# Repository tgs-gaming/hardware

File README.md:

# TGS Hardware

TGS Hardware Projects

[Documentation](docs/README.md)

## TGS INPUT board

[INPUT BOARD USAGE MANUAL](docs/tgs_input_board_usage_manual.md)

Board Configuration Tool

## 

## TGS INPUT/OUTPUT board

## TGS OUTPUT board

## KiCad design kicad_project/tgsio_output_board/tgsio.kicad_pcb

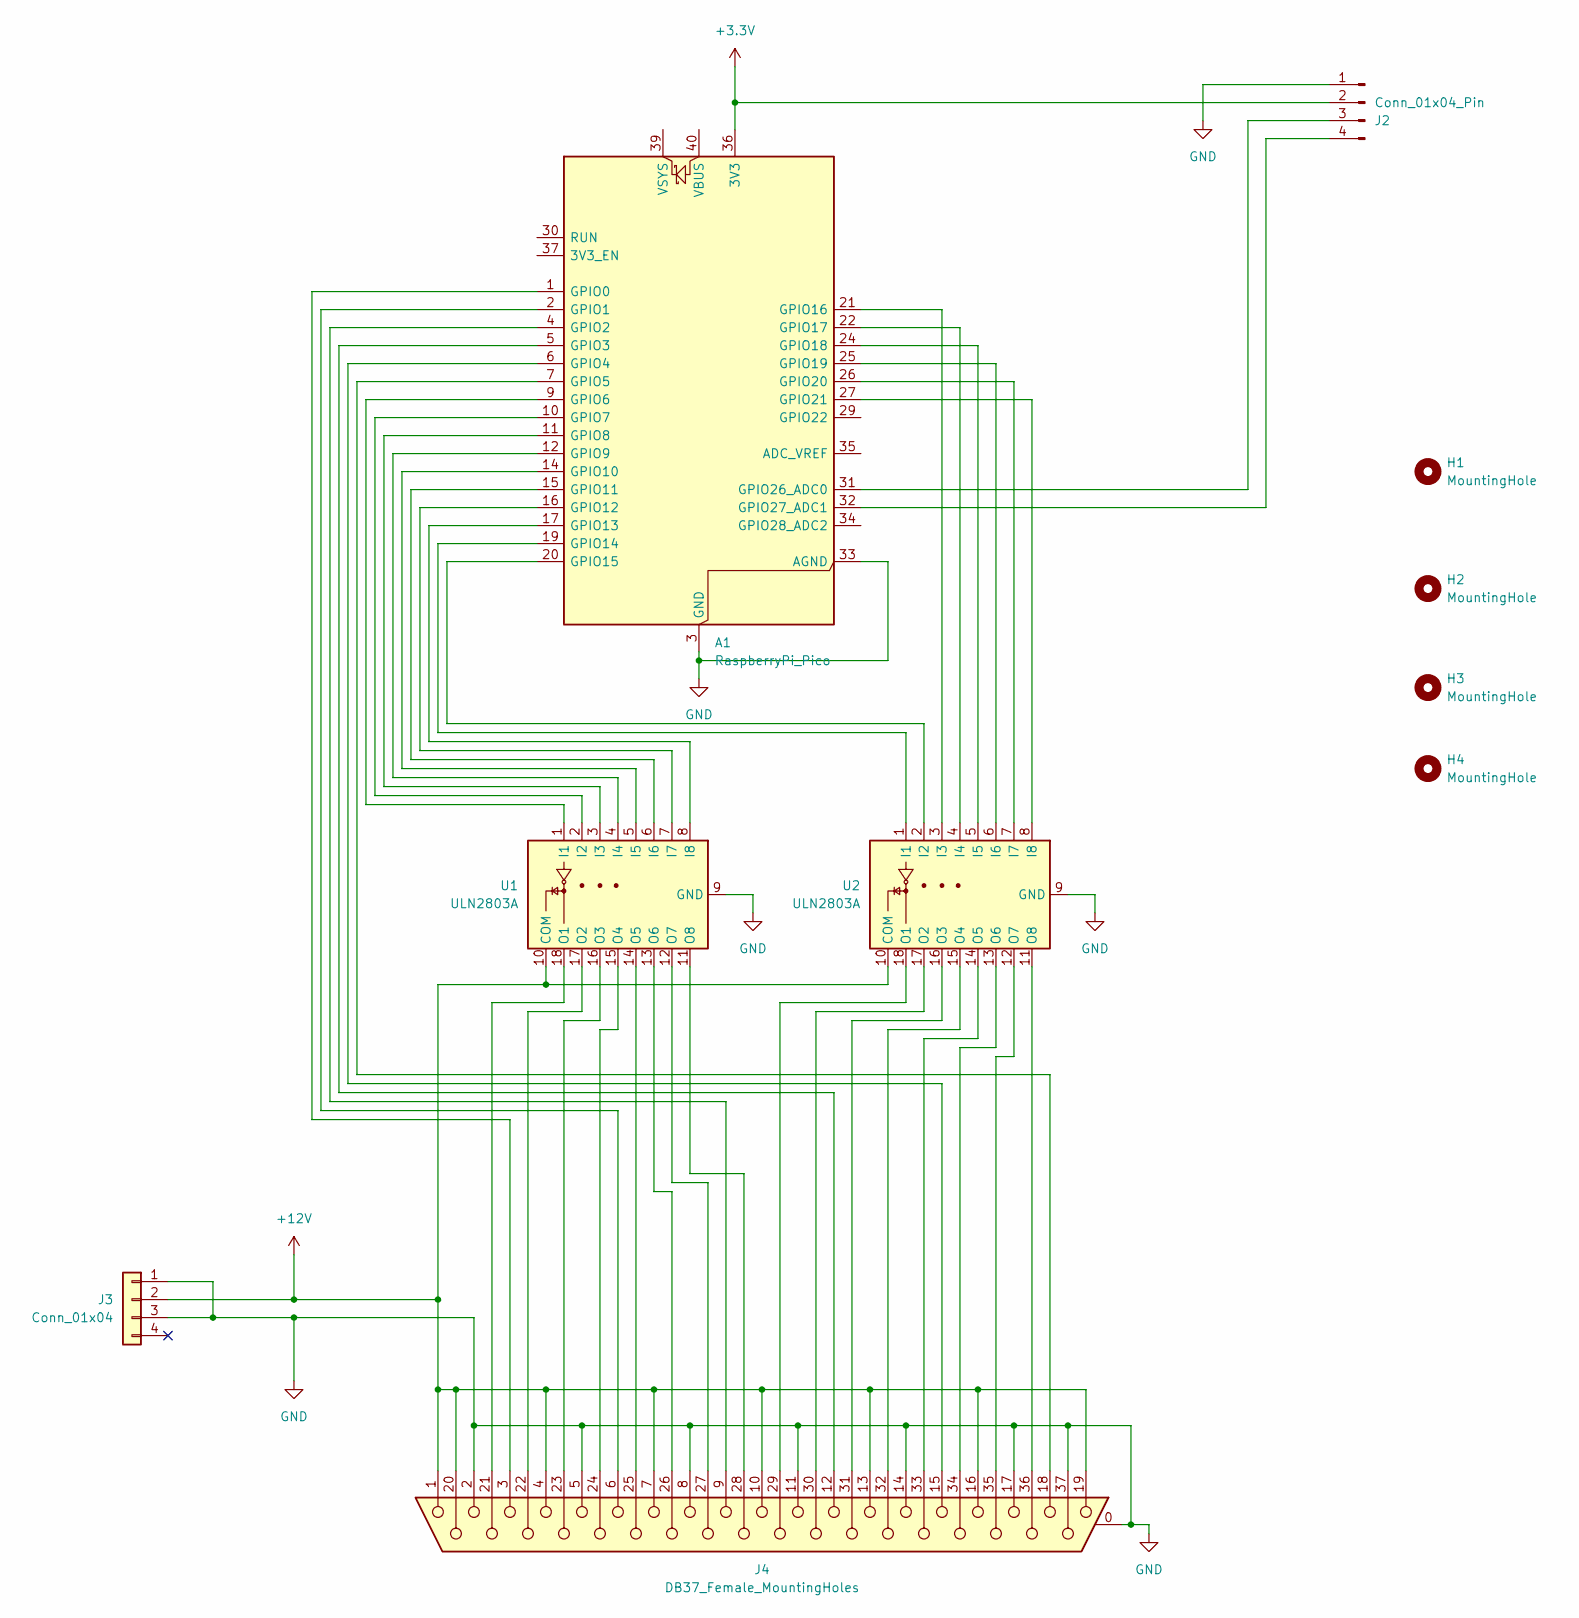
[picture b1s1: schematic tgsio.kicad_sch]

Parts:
A1: RaspberryPi_Pico; RaspberryPi_Pico_Common_Unspecified
H1, H2, H3, H4: MountingHole; MountingHole_3.2mm_M3
J2: Conn_01x04_Pin; JST_PH_B4B-PH-K_1x04_P2.00mm_Vertical
J3: Conn_01x04; Molex_Mini-Fit_Jr_5566-04A_2x02_P4.20mm_Vertical
J4: DB37_Female_MountingHoles; DSUB-37_Female_Horizontal_P2.77x2.84mm_EdgePinOffset4.94mm_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
U1, U2: ULN2803A; DIP-18_W7.62mm_LongPads

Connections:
+3.3V: A1.36 (3V3), J2.2
+12V: J3.2, J4.1, J4.4, J4.7, J4.10, J4.13, J4.16, J4.19, J4.20, U1.10 (COM), U2.10 (COM)
GND: A1.3 (GND), A1.8 (GND), A1.13 (GND), A1.18 (GND), A1.23 (GND), A1.28 (GND), A1.33 (AGND), A1.38 (GND), J2.1, J3.1, J3.3, J4.0 (PAD), J4.2, J4.5, J4.8, J4.11, J4.14, J4.17, J4.37, U1.9 (GND), U2.9 (GND)
unnamed: A1.1 (GPIO0), J4.3
unnamed: A1.2 (GPIO1), J4.6
unnamed: A1.4 (GPIO2), J4.9
unnamed: A1.5 (GPIO3), J4.12
unnamed: A1.6 (GPIO4), J4.15
unnamed: A1.7 (GPIO5), J4.18
unnamed: A1.9 (GPIO6), U1.1 (I1)
unnamed: A1.10 (GPIO7), U1.2 (I2)
unnamed: A1.11 (GPIO8), U1.3 (I3)
unnamed: A1.12 (GPIO9), U1.4 (I4)
unnamed: A1.14 (GPIO10), U1.5 (I5)
unnamed: A1.15 (GPIO11), U1.6 (I6)
unnamed: A1.16 (GPIO12), U1.7 (I7)
unnamed: A1.17 (GPIO13), U1.8 (I8)
unnamed: A1.19 (GPIO14), U2.1 (I1)
unnamed: A1.20 (GPIO15), U2.2 (I2)
unnamed: A1.21 (GPIO16), U2.3 (I3)
unnamed: A1.22 (GPIO17), U2.4 (I4)
unnamed: A1.24 (GPIO18), U2.5 (I5)
unnamed: A1.25 (GPIO19), U2.6 (I6)
unnamed: A1.26 (GPIO20), U2.7 (I7)
unnamed: A1.27 (GPIO21), U2.8 (I8)
unnamed: A1.31 (GPIO26_ADC0), J2.3
unnamed: A1.32 (GPIO27_ADC1), J2.4
unnamed: J4.21, U1.18 (O1)
unnamed: J4.22, U1.17 (O2)
unnamed: J4.23, U1.16 (O3)
unnamed: J4.24, U1.15 (O4)
unnamed: J4.25, U1.14 (O5)
unnamed: J4.26, U1.13 (O6)
unnamed: J4.27, U1.12 (O7)
unnamed: J4.28, U1.11 (O8)
unnamed: J4.29, U2.18 (O1)
unnamed: J4.30, U2.17 (O2)
unnamed: J4.31, U2.16 (O3)
unnamed: J4.32, U2.15 (O4)
unnamed: J4.33, U2.14 (O5)
unnamed: J4.34, U2.13 (O6)
unnamed: J4.35, U2.12 (O7)
unnamed: J4.36, U2.11 (O8)

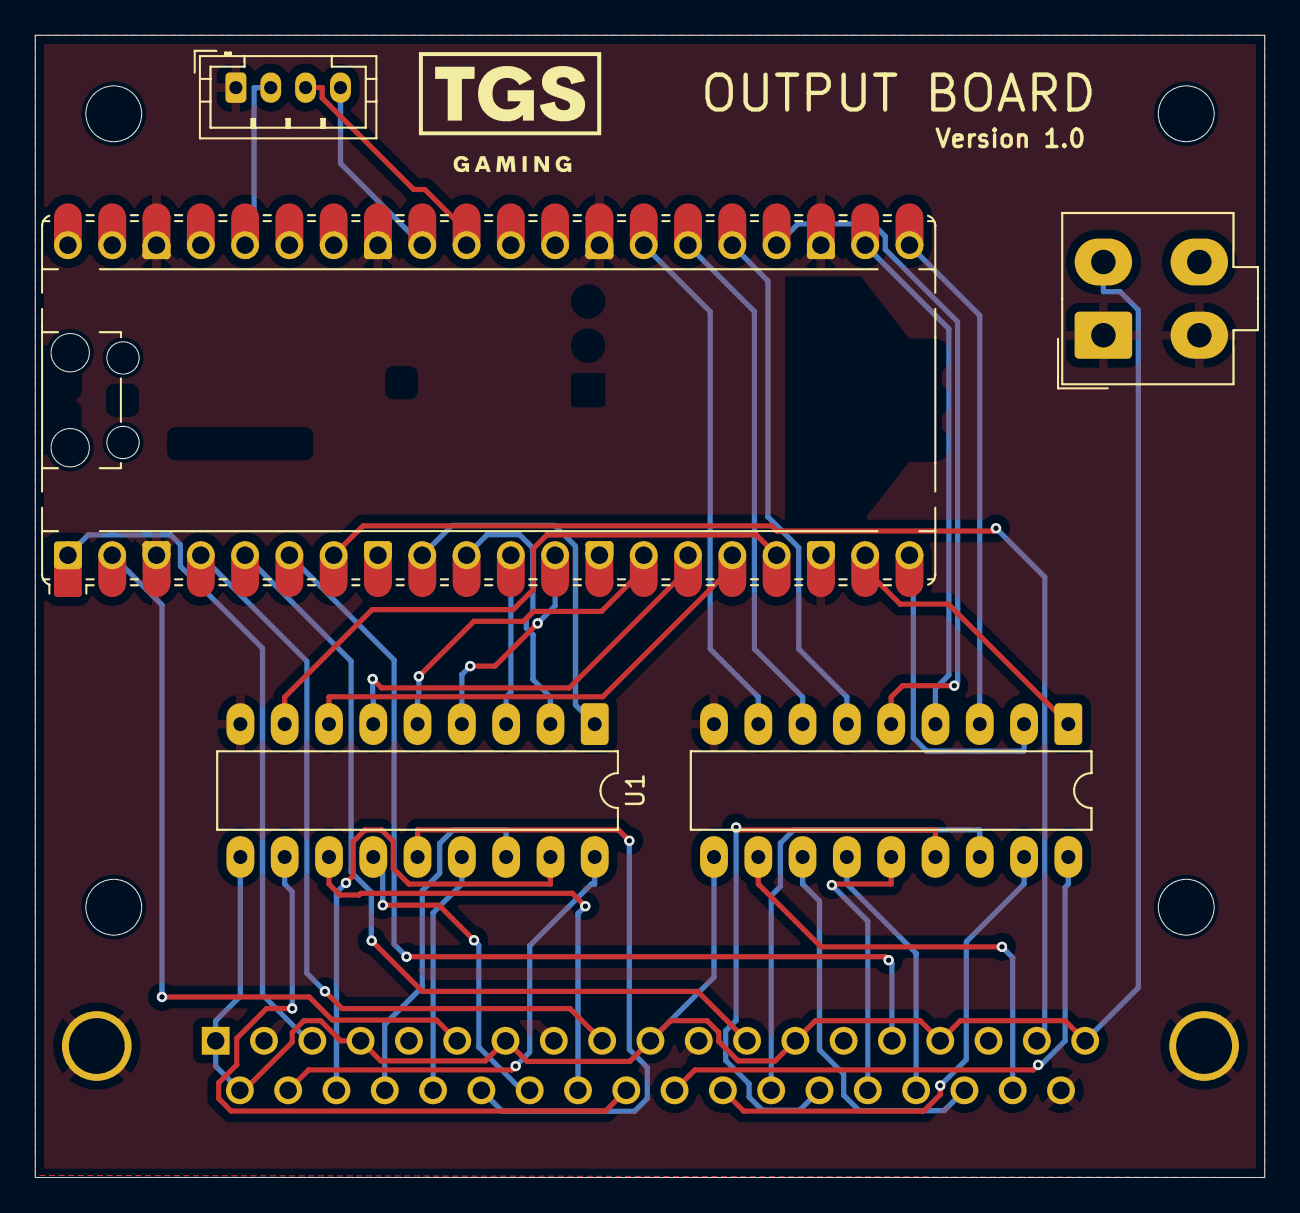
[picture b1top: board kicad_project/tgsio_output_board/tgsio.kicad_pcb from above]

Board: 2 copper layers, 70.5 x 65.5 mm, 10 parts (1 on the bottom side), 43 nets.

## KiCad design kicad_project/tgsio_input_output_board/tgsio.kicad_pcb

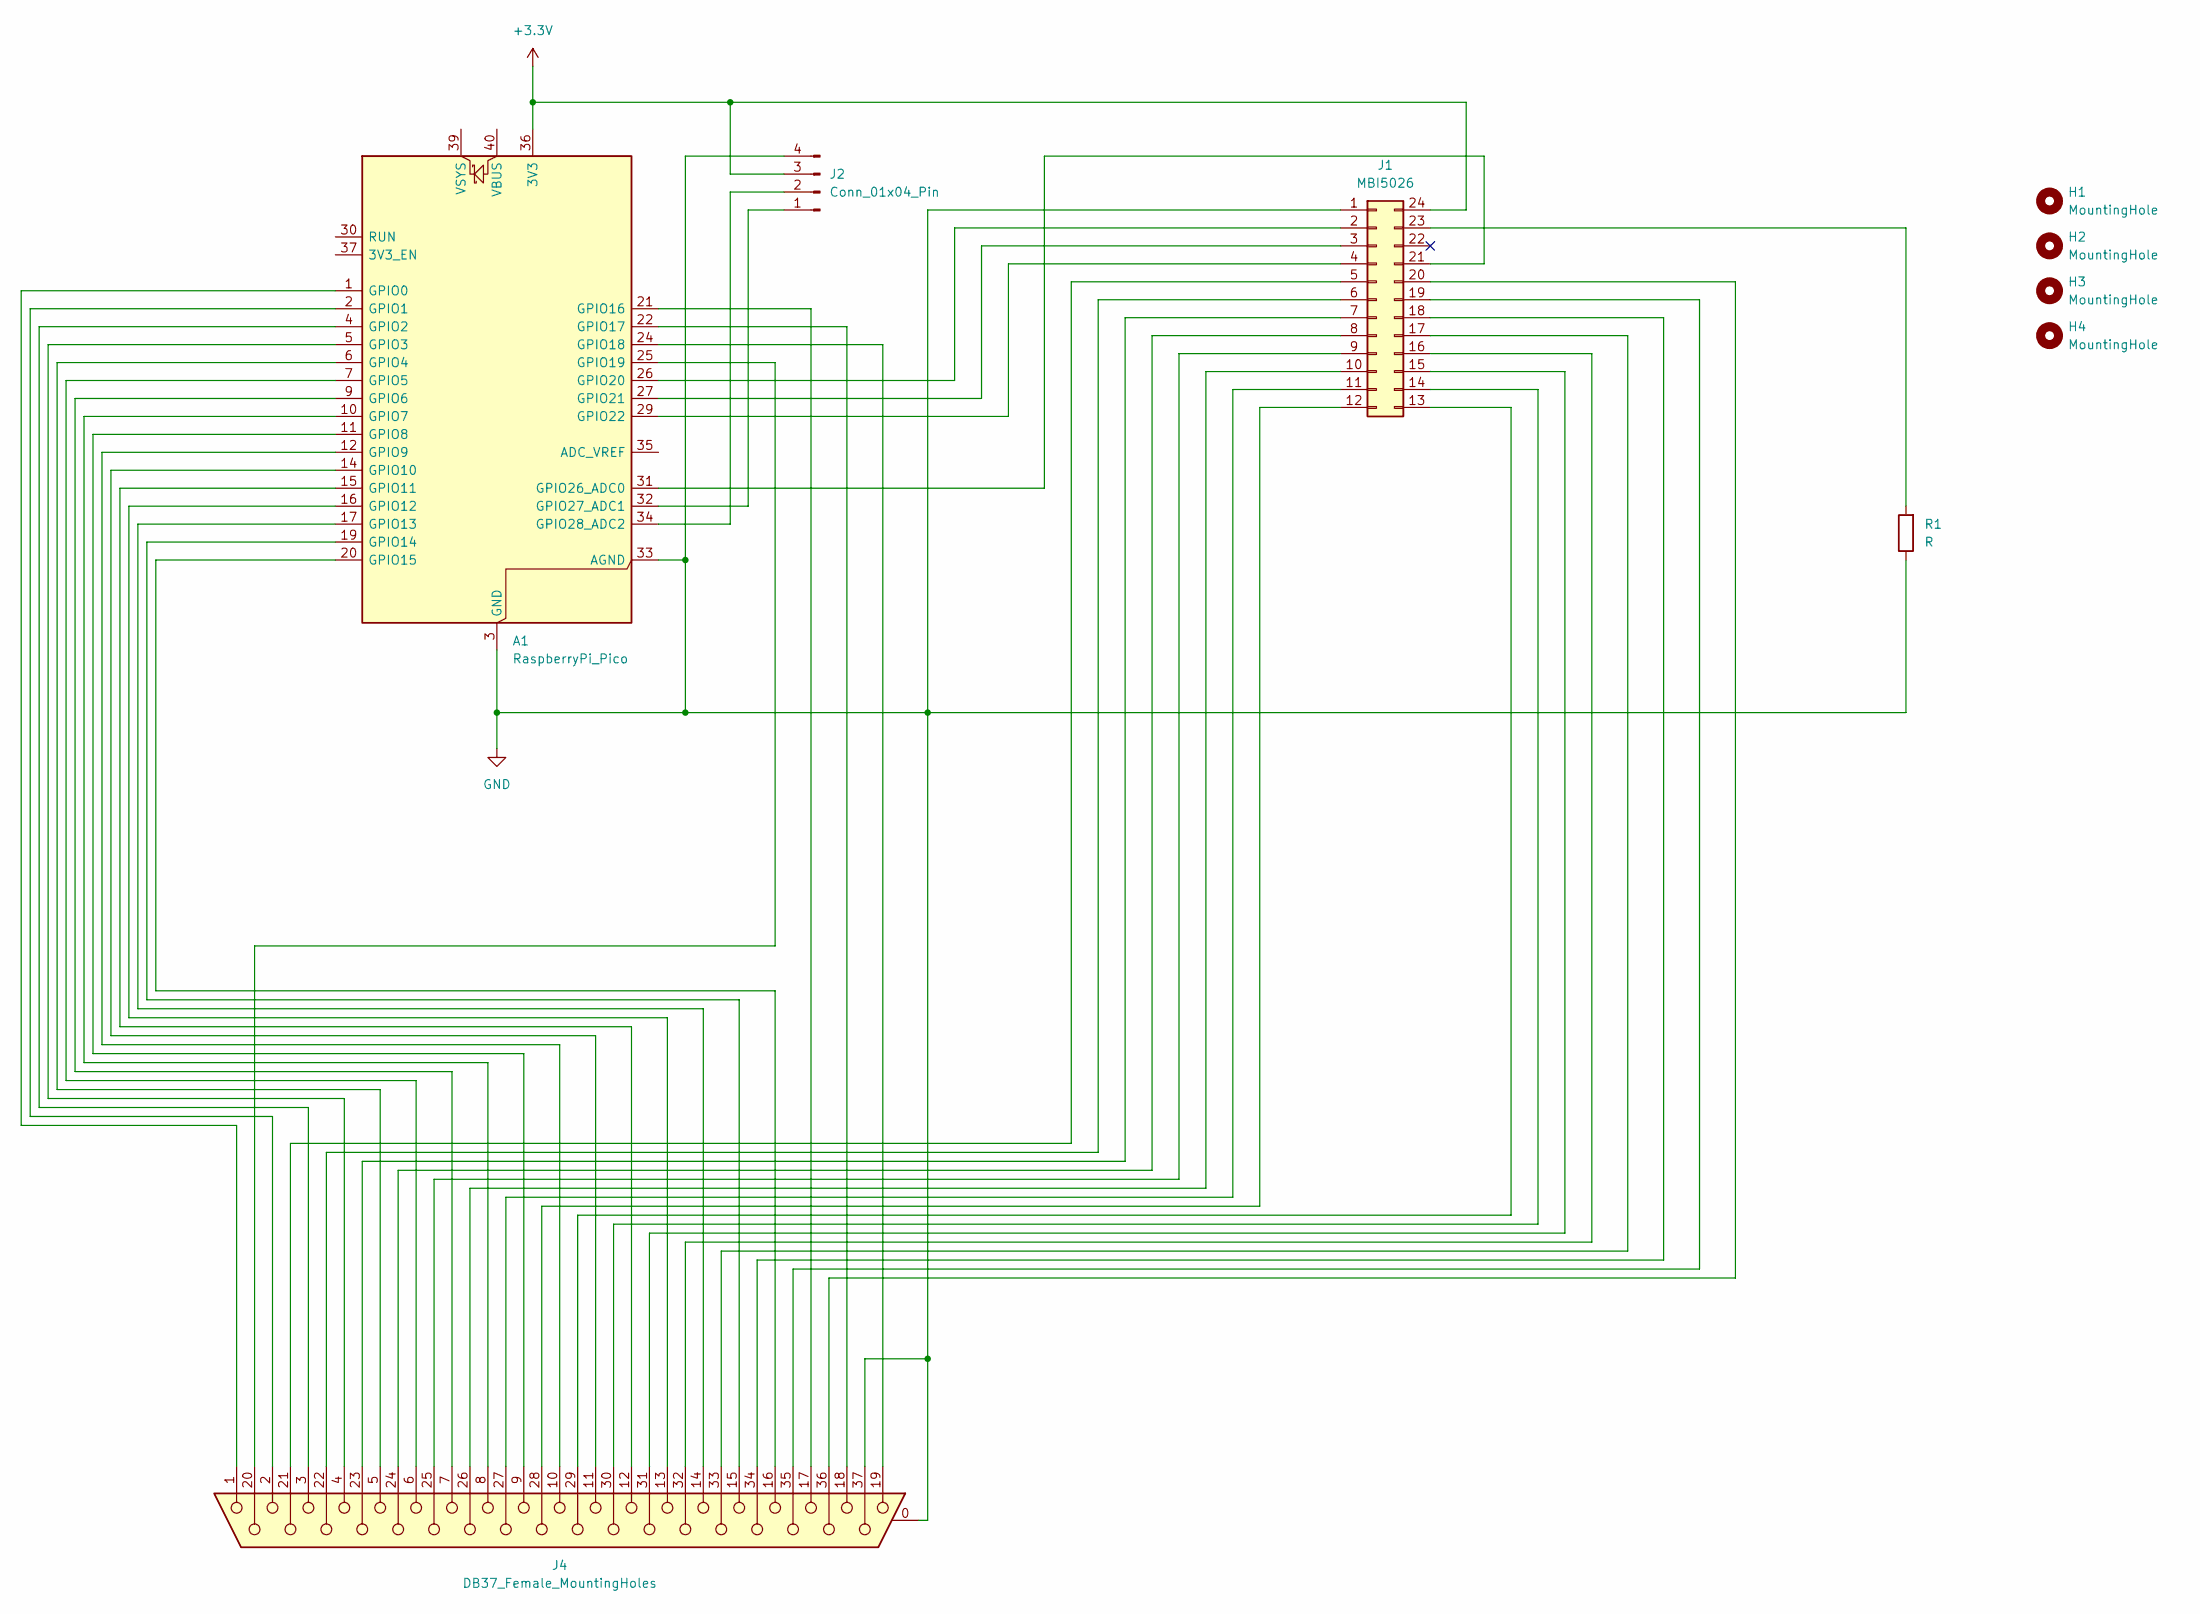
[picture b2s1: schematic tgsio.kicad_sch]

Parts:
A1: RaspberryPi_Pico; RaspberryPi_Pico_Common_SMD
H1, H2, H3, H4: MountingHole; MountingHole_3.2mm_M3
J1: MBI5026; DIP-24_W7.62mm_LongPads
J2: Conn_01x04_Pin; JST_PH_B4B-PH-K_1x04_P2.00mm_Vertical
J4: DB37_Female_MountingHoles; DSUB-37_Female_Horizontal_P2.77x2.84mm_EdgePinOffset4.94mm_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
R1: R; R_Axial_DIN0207_L6.3mm_D2.5mm_P10.16mm_Horizontal

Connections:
+3.3V: A1.36 (3V3), J1.24, J2.3
GND: A1.3 (GND), A1.8 (GND), A1.13 (GND), A1.18 (GND), A1.23 (GND), A1.28 (GND), A1.33 (AGND), A1.38 (GND), J1.1, J2.4, J4.0 (PAD), J4.37, R1.1
unnamed: A1.1 (GPIO0), J4.1
unnamed: A1.2 (GPIO1), J4.2
unnamed: A1.4 (GPIO2), J4.3
unnamed: A1.5 (GPIO3), J4.4
unnamed: A1.6 (GPIO4), J4.5
unnamed: A1.7 (GPIO5), J4.6
unnamed: A1.9 (GPIO6), J4.7
unnamed: A1.10 (GPIO7), J4.8
unnamed: A1.11 (GPIO8), J4.9
unnamed: A1.12 (GPIO9), J4.10
unnamed: A1.14 (GPIO10), J4.11
unnamed: A1.15 (GPIO11), J4.12
unnamed: A1.16 (GPIO12), J4.13
unnamed: A1.17 (GPIO13), J4.14
unnamed: A1.19 (GPIO14), J4.15
unnamed: A1.20 (GPIO15), J4.16
unnamed: A1.21 (GPIO16), J4.17
unnamed: A1.22 (GPIO17), J4.18
unnamed: A1.24 (GPIO18), J4.19
unnamed: A1.25 (GPIO19), J4.20
unnamed: A1.26 (GPIO20), J1.2
unnamed: A1.27 (GPIO21), J1.3
unnamed: A1.29 (GPIO22), J1.4
unnamed: A1.31 (GPIO26_ADC0), J1.21
unnamed: A1.32 (GPIO27_ADC1), J2.1
unnamed: A1.34 (GPIO28_ADC2), J2.2
unnamed: J1.5, J4.21
unnamed: J1.6, J4.22
unnamed: J1.7, J4.23
unnamed: J1.8, J4.24
unnamed: J1.9, J4.25
unnamed: J1.10, J4.26
unnamed: J1.11, J4.27
unnamed: J1.12, J4.28
unnamed: J1.13, J4.29
unnamed: J1.14, J4.30
unnamed: J1.15, J4.31
unnamed: J1.16, J4.32
unnamed: J1.17, J4.33
unnamed: J1.18, J4.34
unnamed: J1.19, J4.35
unnamed: J1.20, J4.36
unnamed: J1.23, R1.2

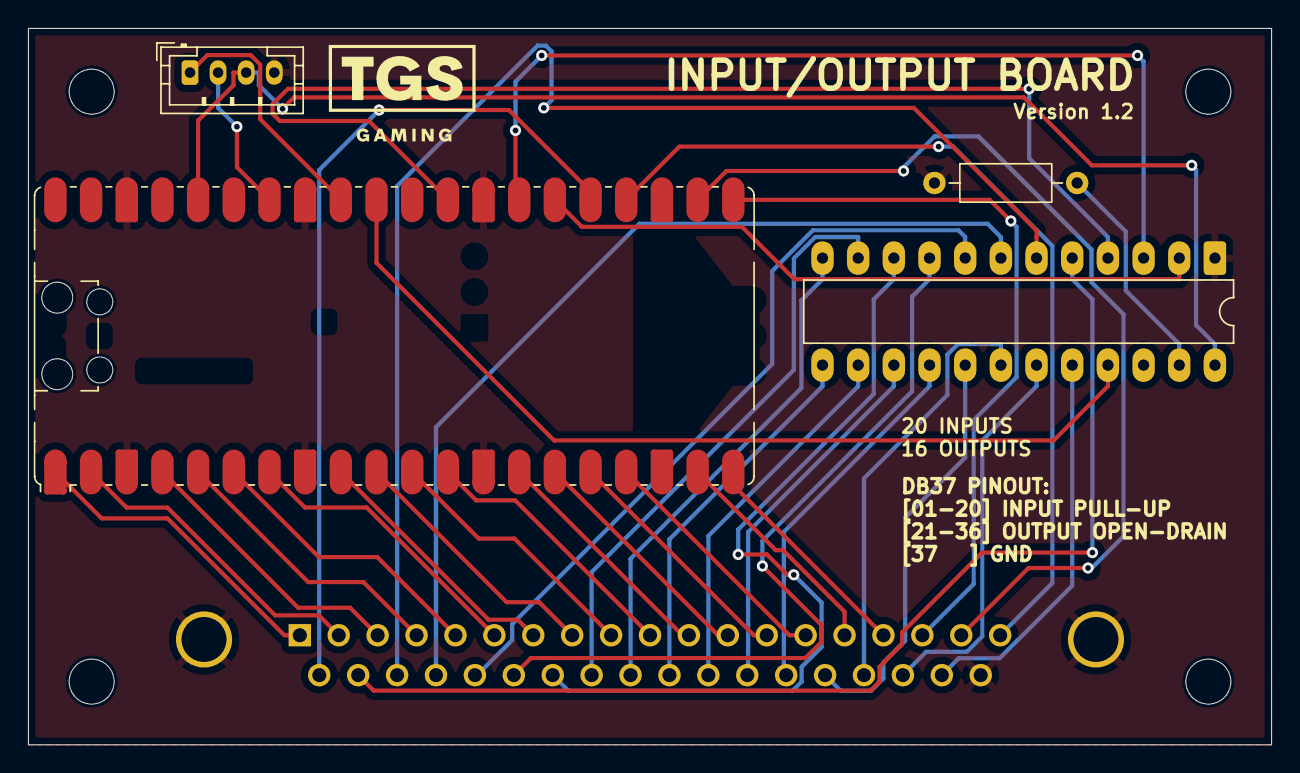
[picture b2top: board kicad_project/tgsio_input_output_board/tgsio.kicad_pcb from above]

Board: 2 copper layers, 88.5 x 51.0 mm, 9 parts (1 on the bottom side), 45 nets.

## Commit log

2025-12-17 First import, added input board source code
2025-12-17 Added kicad git ignore
2025-12-17 Added kicad project files
2026-01-08 Updated routed version
2026-01-08 Added readme
2026-01-09 Updated routing and README
2026-01-16 Added board configuration tool and made some protocol changes
2026-01-17 Load initial state, use on and off instead of closed and opened
